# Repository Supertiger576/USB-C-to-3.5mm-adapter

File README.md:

# About
A straight-forward adapter using a DAC that translates USB-C audio data to 3.5mm.  It takes in the digital USB-C sound data, and then uses the PCM2902 DAC to translate it into analog sound data that can be outputted through a 3.5mm headphone jack.  The PCM2902 DAC is wired following references from it's datasheet. 

# Use
I wanted to make this project as it would be useful for being able to listen to music on the go, without having wireless ear buds.

# Schematic:       

# PCB:      

# 3D Model:    

# Necessary Materials:
|Name                     |Purpose                                                                                           |Quantity|Total Cost (USD)|Link                                                                                                                      |Distributor|
|-------------------------|--------------------------------------------------------------------------------------------------|--------|----------------|--------------------------------------------------------------------------------------------------------------------------|-----------|
|PCB                      |The PCB to put the other components on                                                            |1       |2.00            |https://jlcpcb.com                                                                                                        |JLCPCB     |
|1 uf capacitors          |To connect VC... pins to GND like in the reference sheet.  I only need 6 but buying 10 is cheaper.|10      |0.49            |https://www.digikey.com/en/products/detail/samsung-electro-mechanics/CL21B105KAFNNNE/3886724                              |Digikey    |
|5.6 pF capacitors         |Connecting to the crystal oscillator to handle load                                               |2       |0.22            |https://www.digikey.com/en/products/detail/yageo/CC0805CRNPO9BN5R6/5883902|Digikey    |
|10 uf capacitor          |Capacitor to clear audio on L_out and R_out                                                       |2       |0.60            |https://www.digikey.com/en/products/detail/rubycon/50YXJ10M5X11/3562914                                                   |Digikey    |
|12 MHz Crystal Oscillator|Stable timing on the USBC                                                                         |1       |0.56            |https://www.digikey.com/en/products/detail/kyocera-avx/CX3225SB12000D0GZJC1/5995239                                       |Digikey    |
|1M ohm resistor          |Connected to the crystal oscillator                                                               |1       |0.10            |https://www.digikey.com/en/products/detail/yageo/MFR-25FBF52-1M/13714                                                     |Digikey    |
|DX07P024AJ5R1500         |The usbc plug port for my adapter                                                                 |1       |1.83            |https://www.digikey.com/en/products/detail/jae-electronics/DX07P024AJ5R1500/9169455                                       |Digikey    |
|PCM2902CDBR DAC          |The digital-to-audio converter I will use for my adapter                                          |1       |15.09           |https://www.digikey.com/en/products/detail/texas-instruments/PCM2902CDBR/2780994                                          |Digikey    |
|TRS headphone jack       |The headphone jack at one end of my converter                                                     |1       |0.88            |https://www.digikey.com/en/products/detail/same-sky-formerly-cui-devices/SJ-3523-SMT-TR/281297                            |Digikey    |
|22 ohm resistors         |To connect to D+ and D-                                                                           |2       |0.20            |https://www.digikey.com/en/products/detail/yageo/CFR-50JB-52-22R/1303                                                     |Digikey    |
|5.1k ohm resistors       |To connect to the CC and VCONN channels                                                           |2       |0.20            |https://www.digikey.com/en/products/detail/yageo/CFR-25JT-52-5K1/9098642                                                  |Digikey    |

Made with KiCad

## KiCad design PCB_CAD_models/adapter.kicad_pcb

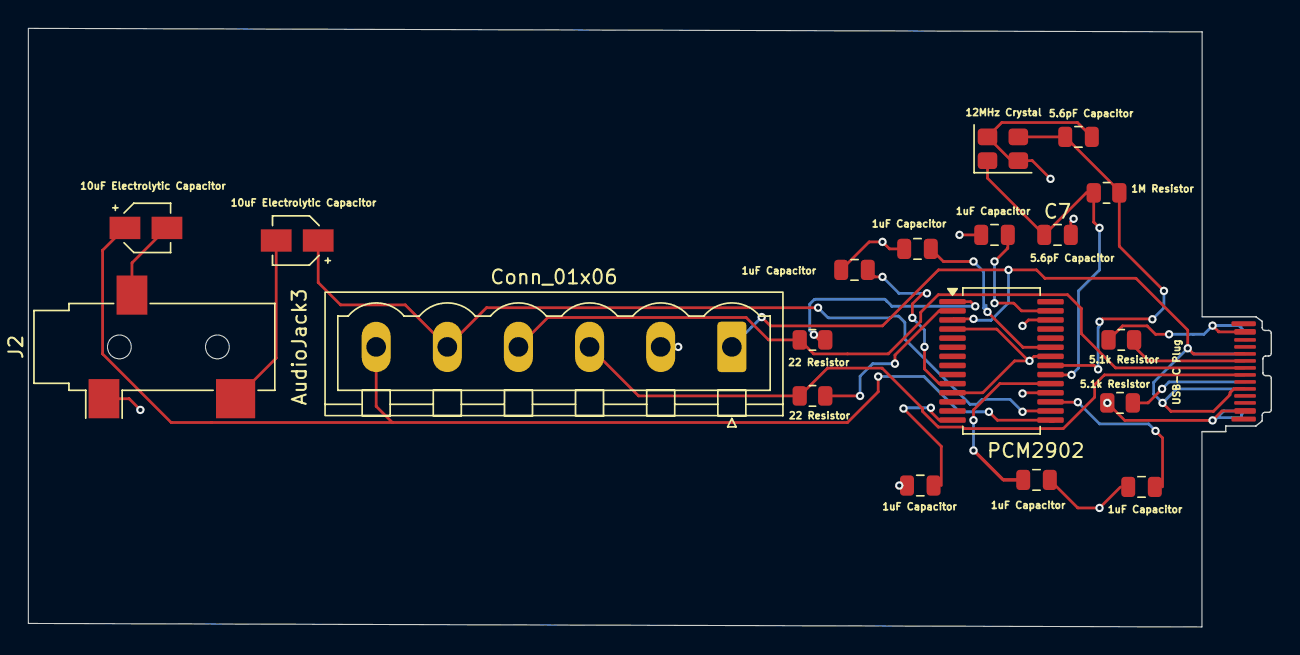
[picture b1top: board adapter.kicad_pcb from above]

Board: 2 copper layers, 88.7 x 42.7 mm, 20 parts (0 on the bottom side), 20 nets.

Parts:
1uF Capacitor, 1uF Capacitor#2: 1uF; C_0805_2012Metric
5.1k Resistor, 5.1k Resistor#2: 5.1k; R_0805_2012Metric
5.6pF Capacitor: 15pF; C_0805_2012Metric
12MHz Crystal : 12 MHz; Crystal_SMD_3225-4Pin_3.2x2.5mm
22 Resistor: 22; R_0805_2012Metric
C2: 1 uF; C_0805_2012Metric
C3: 10uF; CP_Elec_3x5.3
C4: 10uF Electrolytic Capacitor; CP_Elec_3x5.3
C7: 15pF; C_0805_2012Metric
C8, C9, C10: 1uF; C_0805_2012Metric
J1: Conn_01x06; PhoenixContact_MSTBVA_2,5_6-G-5,08_1x06_P5.08mm_Vertical
J2: AudioJack3; Jack_3.5mm_CUI_SJ-3523-SMT_Horizontal
P1: USB-C Plug; USB_C_Plug_JAE_DX07P024AJ1
R4: 22; R_0805_2012Metric
R5: 1M Resistor; R_0805_2012Metric
U1: PCM2902; SSOP-28_5.3x10.2mm_P0.65mm

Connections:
D+: 22 Resistor.2, J1.4 (D+), P1.A6 (D+)
D-: J1.3 (D-), P1.A7 (D-), R4.2
GND: 1uF Capacitor.1, 1uF Capacitor#2.1, 5.1k Resistor.1, 5.1k Resistor#2.1, 5.6pF Capacitor.2, 12MHz Crystal.2 (G), 12MHz Crystal.4 (G), C2.1, C7.2, C8.1, C9.1, C10.1, J1.2 (GND), J2.S, P1.A1 (GND), P1.A12 (GND), P1.B1 (GND), P1.B12 (GND), P1.SH (SHIELD), U1.4 (DGNDU), U1.11 (AGNDC), U1.18 (AGNDP), U1.22 (AGNDX), U1.26 (DGND)
L_out: C3.1, J1.5 (L_out), U1.16 (VOUTL)
unnamed: C3.2, J2.T
unnamed: C4.2, J2.R
unnamed: 5.1k Resistor#2.2, P1.A5 (CC)
unnamed: 5.1k Resistor.2, P1.B5 (VCONN)
unnamed: 22 Resistor.1, U1.1 (D+)
unnamed: R4.1, U1.2 (D-)
unnamed: 1uF Capacitor#2.2, U1.10 (VCCCI)
unnamed: C8.2, U1.17 (VCCP1I)
unnamed: C9.2, U1.19 (VCCP2I)
unnamed: C10.2, U1.23 (VCCXI)
unnamed: 1uF Capacitor.2, U1.14 (VCOM)
unnamed: C2.2, U1.27 (VDDI)
R_out: C4.1, J1.6 (R_out), U1.15 (VOUTR)
VBUS: J1.1 (VBUS), P1.A4 (VBUS), P1.A9 (VBUS), P1.B4 (VBUS), P1.B9 (VBUS), U1.3 (VBUS)
XTI: 5.6pF Capacitor.1, 12MHz Crystal.3, R5.1, U1.21 (XTI)
XTO: 12MHz Crystal.1, C7.1, R5.2, U1.20 (XTO)
